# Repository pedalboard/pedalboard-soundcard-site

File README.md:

# pedalboard-soundcard-site

Source code for github pages avalilable from https://pedalboard.github.io/pedalboard-soundcard-site

This is mostly generated. Do not edit directly!

* latest is generated from main
* latest-x is generated from branch x
* vX.Y.Z are the released versions
* stable points to the current stable release

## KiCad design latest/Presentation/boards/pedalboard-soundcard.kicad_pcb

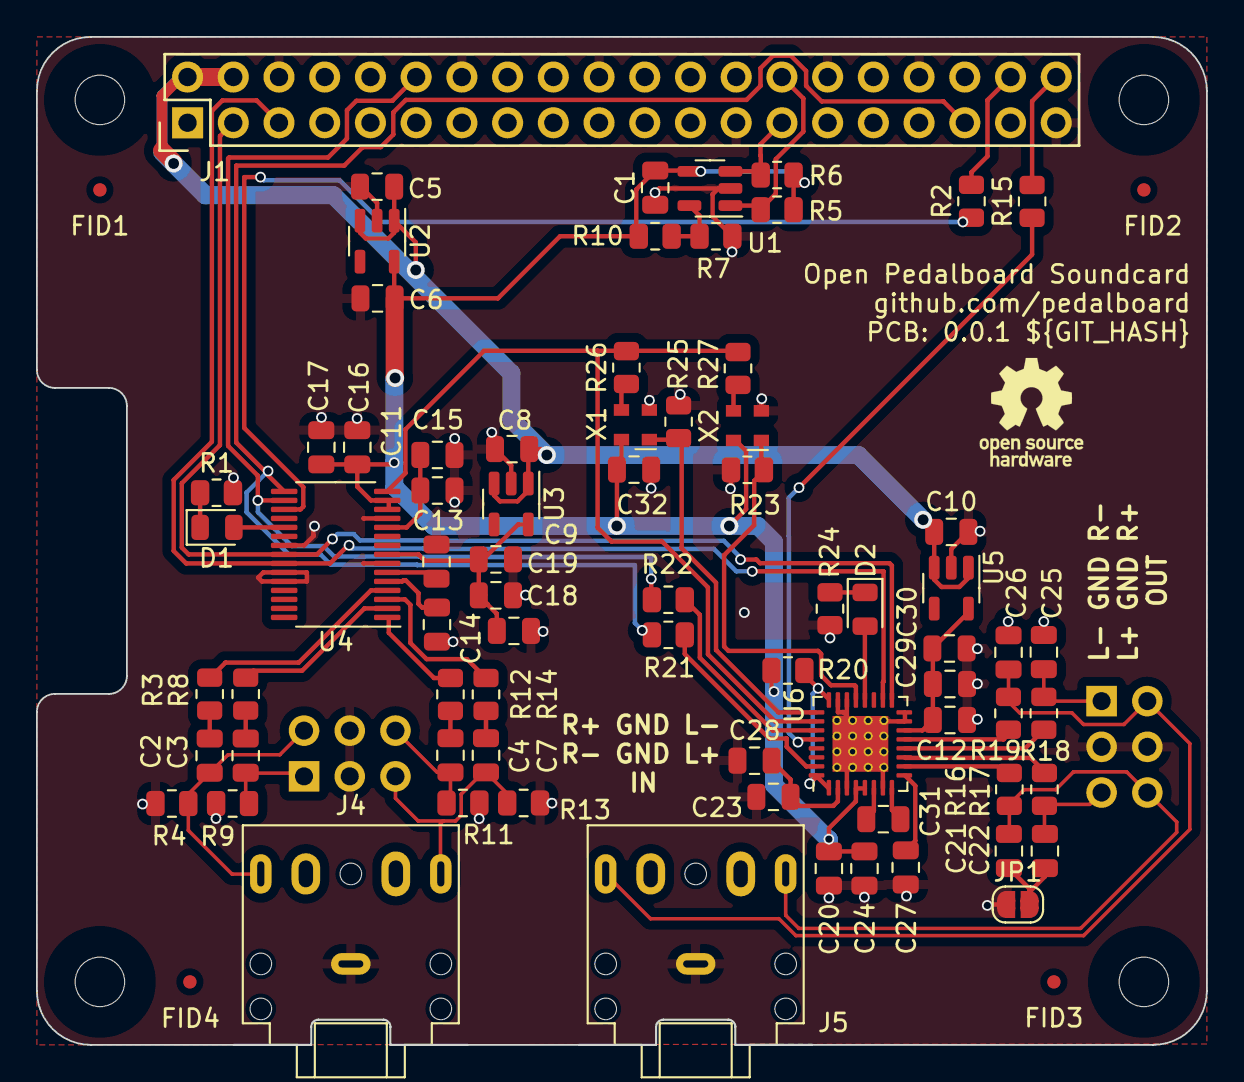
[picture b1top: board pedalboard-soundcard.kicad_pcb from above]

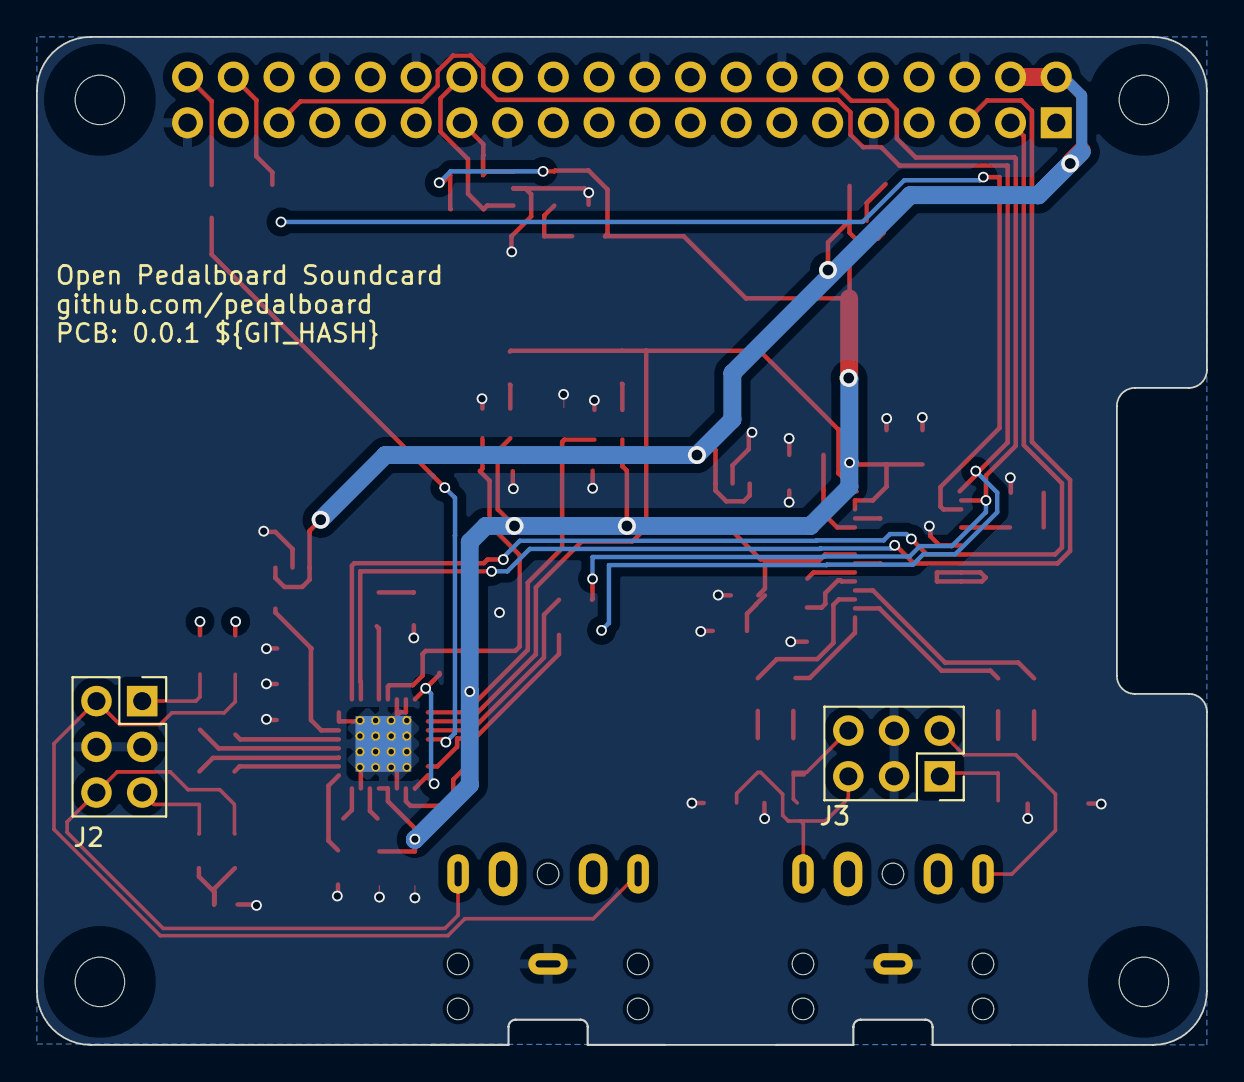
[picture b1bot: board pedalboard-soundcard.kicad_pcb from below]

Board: 2 copper layers, 65.0 x 56.0 mm, 88 parts (2 on the bottom side), 56 nets.

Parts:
C1, C11, C14, C16, C19, C20, C28, C29, C32: 100nF25V; C_0805_2012Metric
C2, C3, C4, C5, C6, C7, C8, C9, C10, C12, C15: 10uF16V; C_0805_2012Metric
C13, C17, C18, C23, C24, C27, C30, C31: 1uF16V; C_0805_2012Metric
C21, C22, C25, C26: 2,2nF50V; C_0805_2012Metric
D1, D2: LED; LED_0805_2012Metric
FID1, FID2, FID3, FID4: Fiducial; Fiducial_0.75mm_Mask1.5mm
H1, H2, H3, H4: MountingHole; RPi_Hat_Mounting_Hole
J1: RPi_GPIO; Pin_Header_Straight_2x20
J2, J3: Conn_02x03_Odd_Even; PinSocket_2x03_P2.54mm_Vertical
J4, J5: Audio_Jack; Jack_3.5mm_CUI_SJ1-3525N_Horizontal
JP1: SJP; SolderJumper-2_P1.3mm_Open_RoundedPad1.0x1.5mm
R1, R20, R23, R24, R25: 10K; R_0805_2012Metric
R2, R3, R8, R12, R14, R15, R21, R22, R26, R27: 100R; R_0805_2012Metric
R4, R9, R11, R13: 100K; R_0805_2012Metric
R5, R6, R7, R10: 3K9; R_0805_2012Metric
R16, R17, R18, R19: 470R; R_0805_2012Metric
SYM1: Logo_Open_Hardware_Small; OSHW-Logo_5.7x6mm_SilkScreen
T1, T2, T3, T4: Tab
U1: AT24CS01-STUM; SOT-23-5
U2, U3, U5: NCP163; SOT-23-5
U4: PCM1863DBT; TSSOP-30_4.4x7.8mm_P0.5mm
U6: PCM5242RHBR; HVQFN-32-1EP_5x5mm_P0.5mm_EP3.1x3.1mm_ThermalVias
X1: 22.5792Mhz; Oscillator_SMD_Abracon_ASDMB-4Pin_2.5x2.0mm
X2: 24.576Mhz; Oscillator_SMD_Abracon_ASDMB-4Pin_2.5x2.0mm

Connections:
+5V: C5.1, C8.1, C10.1, J1.2 (5V), J1.4 (5V), U2.1 (IN), U2.3 (EN), U3.1 (IN), U3.3 (EN), U5.1 (IN), U5.3 (EN)
/ADC/inl+: C7.2, J3.5, J4.T, R13.2
/ADC/inl-: C4.2, J3.6, R11.2
/ADC/inr+: C2.2, J3.2, J4.R, R4.2
/ADC/inr-: C3.2, J3.1, R9.2
/DAC/outl+: C21.1, J2.6, J5.T, R16.2
/DAC/outl-: C22.1, J2.5, R17.2
/DAC/outr+: C26.1, J2.2, J5.R, R19.2
/DAC/outr-: C25.1, J2.1, R18.2
/ID_SC: J1.28 (BCM1_ID_SC), R5.1, U1.1 (SCL)
/ID_SD: J1.27 (BCM0_ID_SD), R6.1, U1.3 (SDA)
DIN: R15.1, U6.28 (DIN)
DOUT: J1.38 (BCM20_MOSI_PCM_DI), R2.2
GND: C1.1, C5.2, C6.2, C8.2, C9.2, C10.2, C11.2, C12.2, C13.1, C14.1, C15.2, C16.2, C17.2, C18.2, C19.2, C20.1, C23.1, C24.1, C27.1, C28.1, C29.2, C30.1, C32.2, J1.6 (GND), J1.9 (GND), J1.14 (GND), J1.20 (GND), J1.25 (GND), J1.30 (GND), J1.34 (GND), J1.39 (GND), J2.3, J2.4, J3.3, J3.4, J4.S, J5.S, JP1.1 (A), R1.2, R4.1, R7.2, R9.1, R11.1, R13.1, R23.2, R24.1, R25.2, U1.2 (GND), U2.2 (GND), U3.2 (GND), U4.7 (AGND), U4.12 (DGND), U4.22 (MISO/GPIO0/DMIN2), U4.25 (MS/AD), U4.26 (MD0), U5.2 (GND), U6.3 (DGND), U6.7 (CPGND), U6.15 (AGND), U6.16 (VCOM), U6.22 (ADR2), U6.23 (MODE1), U6.33 (EPAD), X1.2 (GND), X2.2 (GND)
unnamed: C2.1, R3.2
unnamed: C3.1, R8.2
unnamed: C4.1, R12.2
unnamed: C7.1, R14.2
unnamed: D1.2 (A), U4.20 (GPIO2/INTB/DMCLK)
unnamed: D1.1 (K), R1.1
unnamed: D2.2 (A), U6.20 (GPIO4)
unnamed: D2.1 (K), R24.2
unnamed: J1.40 (BCM21_SCLK_PCM_DO), R15.2
unnamed: C21.2, C22.2, C25.2, C26.2, JP1.2 (B)
unnamed: R7.1, R10.2, U1.5 (WP)
unnamed: R2.1, U4.18 (DOUT)
unnamed: C11.1, C15.1, U4.11 (LDO)
unnamed: R14.1, U4.3 (VINL1/VIN1P)
unnamed: R12.1, U4.1 (VINL2/VIN1M)
unnamed: R3.1, U4.4 (VINR1/VIN2P)
unnamed: R8.1, U4.2 (VINR2/VIN2M)
unnamed: C13.2, U4.6 (VREF)
unnamed: R20.1, U6.1 (XSMT), U6.24 (MODE2), U6.32 (ADR1)
unnamed: R22.2, U6.27 (BCK)
unnamed: C31.1, U6.8 (CAPM)
unnamed: C31.2, U6.6 (CAPP)
unnamed: R23.1, U6.21 (GPIO3), X2.1 (Tri-State)
unnamed: R25.1, U6.25 (GPIO6), X1.1 (Tri-State)
unnamed: C23.2, C28.2, U6.2 (LDOO)
unnamed: R21.2, U6.31 (LRCK)
unnamed: R17.1, U6.11 (OUTLN)
unnamed: R16.1, U6.10 (OUTLP)
unnamed: R18.1, U6.12 (OUTRN)
unnamed: R19.1, U6.13 (OUTRP)
unnamed: C27.2, U6.9 (VNEG)
unnamed: R26.1, X1.3 (OUT)
unnamed: R27.1, X2.3 (OUT)
VDD: C1.2, C6.1, C16.1, C17.1, C20.2, C24.2, C32.1, R5.2, R6.2, R10.1, R20.2, U1.4 (VCC), U2.5 (OUT), U4.13 (DVDD), U4.14 (IOVDD), U6.4 (DVDD), U6.5 (CPVDD), X1.4 (VDD), X2.4 (VDD)
VDDA: C12.1, C29.1, C30.2, U5.5 (OUT), U6.14 (AVDD)
VDDF: C9.1, C18.1, C19.1, U3.5 (OUT), U4.8 (AVDD)
master_clk: R26.2, R27.2, U4.15 (SCKI), U6.26 (SCK)
micbias: C14.2, U4.5 (MICBIAS)
pcm_clk: J1.12 (BCM18_PCM_C), R22.1, U4.17 (BCK)
pcm_fs: J1.35 (BCM19_MISO_PCM_FS), R21.1, U4.16 (LRCK)
scl: J1.5 (BCM3_SCL), U4.24 (MC/SCL), U6.18 (SCL)
sda: J1.3 (BCM2_SDA), U4.23 (MOSI/SDA), U6.17 (SDA)

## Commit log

2023-12-23 Deploying to main from @ pedalboard/pedalboard-soundcard@93a852f3930618f236384819ef2fcf7df03ddc93 🚀
2023-12-23 Deploying to main from @ pedalboard/pedalboard-soundcard@3a51d1952a1cfa062257a61bb80e93aedc8dfe00 🚀
2023-12-23 Deploying to main from @ pedalboard/pedalboard-soundcard@f177819ae6f0370ab94271f90f51836291559134 🚀
2023-12-23 Deploying to main from @ pedalboard/pedalboard-soundcard@4573beb280238f02b8ae2719e893d8cb8154c0eb 🚀
2023-12-23 Deploying to main from @ pedalboard/pedalboard-soundcard@a7bd26fa649fc33af0f3bdc4ee1db45b1dd59ae4 🚀
2023-12-23 Deploying to main from @ pedalboard/pedalboard-soundcard@558ba371ddace54d417bbda5e9fd33c27c28cf43 🚀
2023-12-23 Deploying to main from @ pedalboard/pedalboard-soundcard@121651b79071cabd967c3fdaa6a5b4df972337c6 🚀
2023-12-23 Deploying to main from @ pedalboard/pedalboard-soundcard@b26d7a67c024050b4e711af8762d08fb9c7b49c0 🚀
2023-12-23 Deploying to main from @ pedalboard/pedalboard-soundcard@fccd8dcd0f263d8aa2e37b7888e7cb8de8e83f90 🚀
2023-12-26 Deploying to main from @ pedalboard/pedalboard-soundcard@0488faa66560b37433c7e0f4344898171c2572cd 🚀
2023-12-27 Deploying to main from @ pedalboard/pedalboard-soundcard@9ff71caa1bead3e39e970fb8eb00afcc969b1d95 🚀
2023-12-27 Deploying to main from @ pedalboard/pedalboard-soundcard@68bb33b14d3c2964e6c94e09ff8f1b2e324aa4e3 🚀
2023-12-27 Deploying to main from @ pedalboard/pedalboard-soundcard@178cb6866e2ac14b6a456bf1f3c4dd0ad9013d24 🚀
2023-12-27 Deploying to main from @ pedalboard/pedalboard-soundcard@a953afb97768343eb7c0c70254a11cd91df6115a 🚀
2023-12-27 Deploying to main from @ pedalboard/pedalboard-soundcard@68d51a93a771657fbf448573140af5b936464317 🚀
2023-12-27 Deploying to main from @ pedalboard/pedalboard-soundcard@acfb235101f16f8e9376b91e1b06100ef68de74e 🚀
2023-12-27 Deploying to main from @ pedalboard/pedalboard-soundcard@a8dd871aa4398d93fdc1f6e8393f8e9399b7e40f 🚀
2023-12-27 Deploying to main from @ pedalboard/pedalboard-soundcard@edabd6e6ce32d1168237b1e9e6bd9c8dcb412e94 🚀
2023-12-27 Deploying to main from @ pedalboard/pedalboard-soundcard@b66a0555f33d5c42be95f3ccf42685ac35097389 🚀
2023-12-27 Deploying to main from @ pedalboard/pedalboard-soundcard@2fa00d5ba3cc51df554dc1664a8161fb31355fdc 🚀
2023-12-27 Deploying to main from @ pedalboard/pedalboard-soundcard@1880acdf820630834144e4f73a6cb894e7d362d5 🚀
2023-12-27 Deploying to main from @ pedalboard/pedalboard-soundcard@fa517cd6c6d790ce1d19759159959b11625ddacd 🚀
2023-12-27 Deploying to main from @ pedalboard/pedalboard-soundcard@b06d7cb0fe11a40b7e32f8b0f12bc6f70bdd600b 🚀
2023-12-27 Deploying to main from @ pedalboard/pedalboard-soundcard@eef4807614ca3b53a2e1f0c4e61958f035bbd554 🚀
2023-12-27 Deploying to main from @ pedalboard/pedalboard-soundcard@99363dd4079ad7a35a02145145f80d1bef758339 🚀
2023-12-27 Deploying to main from @ pedalboard/pedalboard-soundcard@e9993308803a85a712f85b8a2b63a62976777825 🚀
2023-12-28 Deploying to main from @ pedalboard/pedalboard-soundcard@0f469fbddc75dd4a029d9494f2b0c59c5803a2b9 🚀
2023-12-28 Deploying to main from @ pedalboard/pedalboard-soundcard@8aee33d1b86638a79d6a7e5ddf42295d98a046b5 🚀
2023-12-28 Deploying to main from @ pedalboard/pedalboard-soundcard@45797088e94bfd3d678359e2b04b959829b5edab 🚀
2024-01-07 Deploying to main from @ pedalboard/pedalboard-soundcard@51e976a959ffa8df3bec8cdd28ef2bbfe6ee9dac 🚀
2024-01-07 Deploying to main from @ pedalboard/pedalboard-soundcard@280026019d5335fa30d3bd7b9a04d58a719db5f7 🚀
2024-01-07 Deploying to main from @ pedalboard/pedalboard-soundcard@fe843296827acb3f5b92ffba67a5b8e2b952370c 🚀
2024-01-07 Deploying to main from @ pedalboard/pedalboard-soundcard@c48074776f7170f021416f276aaf44984625ac1c 🚀
2024-03-12 Deploying to main from @ pedalboard/pedalboard-soundcard@16e20904120cd027ee11319bee1124aa5c01cfd9 🚀
2024-10-04 Deploying to main from @ pedalboard/pedalboard-soundcard@5062527d60d1d7cefc9884fb6fbaf3b1f6e79b11 🚀
2024-10-04 Deploying to main from @ pedalboard/pedalboard-soundcard@ef06bb3a7dd2e514dd16f3b134ff966dda655ad9 🚀
2024-10-04 Deploying to main from @ pedalboard/pedalboard-soundcard@1730fbf9da6e031e8bac9260703ce939930d5b8e 🚀
2024-10-04 Deploying to main from @ pedalboard/pedalboard-soundcard@472fddb527b6d6c1791c513fb6cce67eb2687b5b 🚀
2024-10-14 Deploying to main from @ pedalboard/pedalboard-soundcard@1db40af0f6ab3e1fe95bb8dbdb53da2246832402 🚀
2024-10-15 Deploying to main from @ pedalboard/pedalboard-soundcard@cb641f7770a1cd062746c3691cf60e673af2823d 🚀
2024-10-16 Deploying to main from @ pedalboard/pedalboard-soundcard@c8ff8143bd6d3519a289d2009de94ac11b01fc0e 🚀
2024-10-16 Deploying to main from @ pedalboard/pedalboard-soundcard@3fe660e3b4f521427d2bd7254f43d15b487a28a1 🚀
2024-10-16 Deploying to main from @ pedalboard/pedalboard-soundcard@e635f868f6b7192102ab83f1095ac231ae29b730 🚀
2024-10-16 Deploying to main from @ pedalboard/pedalboard-soundcard@734a022232cb1d83cff70071d8b12865fc63a3ab 🚀
2024-10-16 Deploying to main from @ pedalboard/pedalboard-soundcard@a6473a2c66b38504b0732739983247241ec507bb 🚀
2024-10-16 Deploying to main from @ pedalboard/pedalboard-soundcard@9e9bf81c976ebc61bc46c88f3918851767b93e75 🚀
2024-10-16 v1.0.0
2024-10-16 Deploying to main from @ pedalboard/pedalboard-soundcard@695ad573ad28e992da1e594383c4e203e519cfa1 🚀
2024-10-17 Deploying to main from @ pedalboard/pedalboard-soundcard@d86a8cf2d7602bdbbdcce72082a44764389d3acd 🚀
2024-12-15 Deploying to main from @ pedalboard/pedalboard-soundcard@f453ff3d504841b6952750bd6e648f4d40e042b1 🚀
2024-12-15 Deploying to main from @ pedalboard/pedalboard-soundcard@05a17fdb1a47ef051d8d661718491cc3050219a2 🚀
2024-12-15 Deploying to main from @ pedalboard/pedalboard-soundcard@26f3ca50cc2e0b2273ee93242bc51fa4416f000b 🚀
2024-12-15 Deploying to main from @ pedalboard/pedalboard-soundcard@2643d83852633497b8056ec2bf14a906d9eac8b9 🚀
2024-12-15 Deploying to main from @ pedalboard/pedalboard-soundcard@83512e23caeb9f9e6588580479b630e98423341c 🚀
2024-12-15 Deploying to main from @ pedalboard/pedalboard-soundcard@3b0e830a0e3d2faae250be5665aca3481b2d88f2 🚀
2024-12-15 Deploying to main from @ pedalboard/pedalboard-soundcard@ff64d0007a03d3480823d54c9564f3638745a3c2 🚀
2024-12-16 Deploying to main from @ pedalboard/pedalboard-soundcard@13ce387b1c0433f84da0b517618d1037b3e64a3f 🚀
2025-04-21 Deploying to main from @ pedalboard/pedalboard-soundcard@69be3e94ce32679f967c18c75666e25729b23b69 🚀
2025-04-21 Deploying to main from @ pedalboard/pedalboard-soundcard@fdfc2796516e064c8d8c52354f949af6a5cb7c4b 🚀
2025-04-21 Deploying to main from @ pedalboard/pedalboard-soundcard@614a087db432473d265999709cdb653bccf0bcb8 🚀
2025-04-21 Deploying to main from @ pedalboard/pedalboard-soundcard@d4f3fb0454159726fa0742c15d7a1e8d2ec19fd9 🚀

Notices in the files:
latest/Presentation/boards/pedalboard-soundcard.kicad_pcb:
License: CERN Open Hardware Licence Version 2 - Permissive
